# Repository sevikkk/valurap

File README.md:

Next iteration of 3d printer
============================

Hardware
--------

* 20x20 and 20x40 v-profile, linear rails based on PVC rollers
* E3D Titan Aero Extruder

Electronics
-----------

* Orange PI Zero as main brains and network
* Mojo v3 as FPGA
* TMC2130 Stepper drivers

Directories
-----------

* fpga/ - verilog sources for SLX9 on Mojo 
* mojo_soft/ - software for mega32u4 on Mojo
* host_soft/ - python sources running on Zero
* pcbs/ - KiCad files for PCBs

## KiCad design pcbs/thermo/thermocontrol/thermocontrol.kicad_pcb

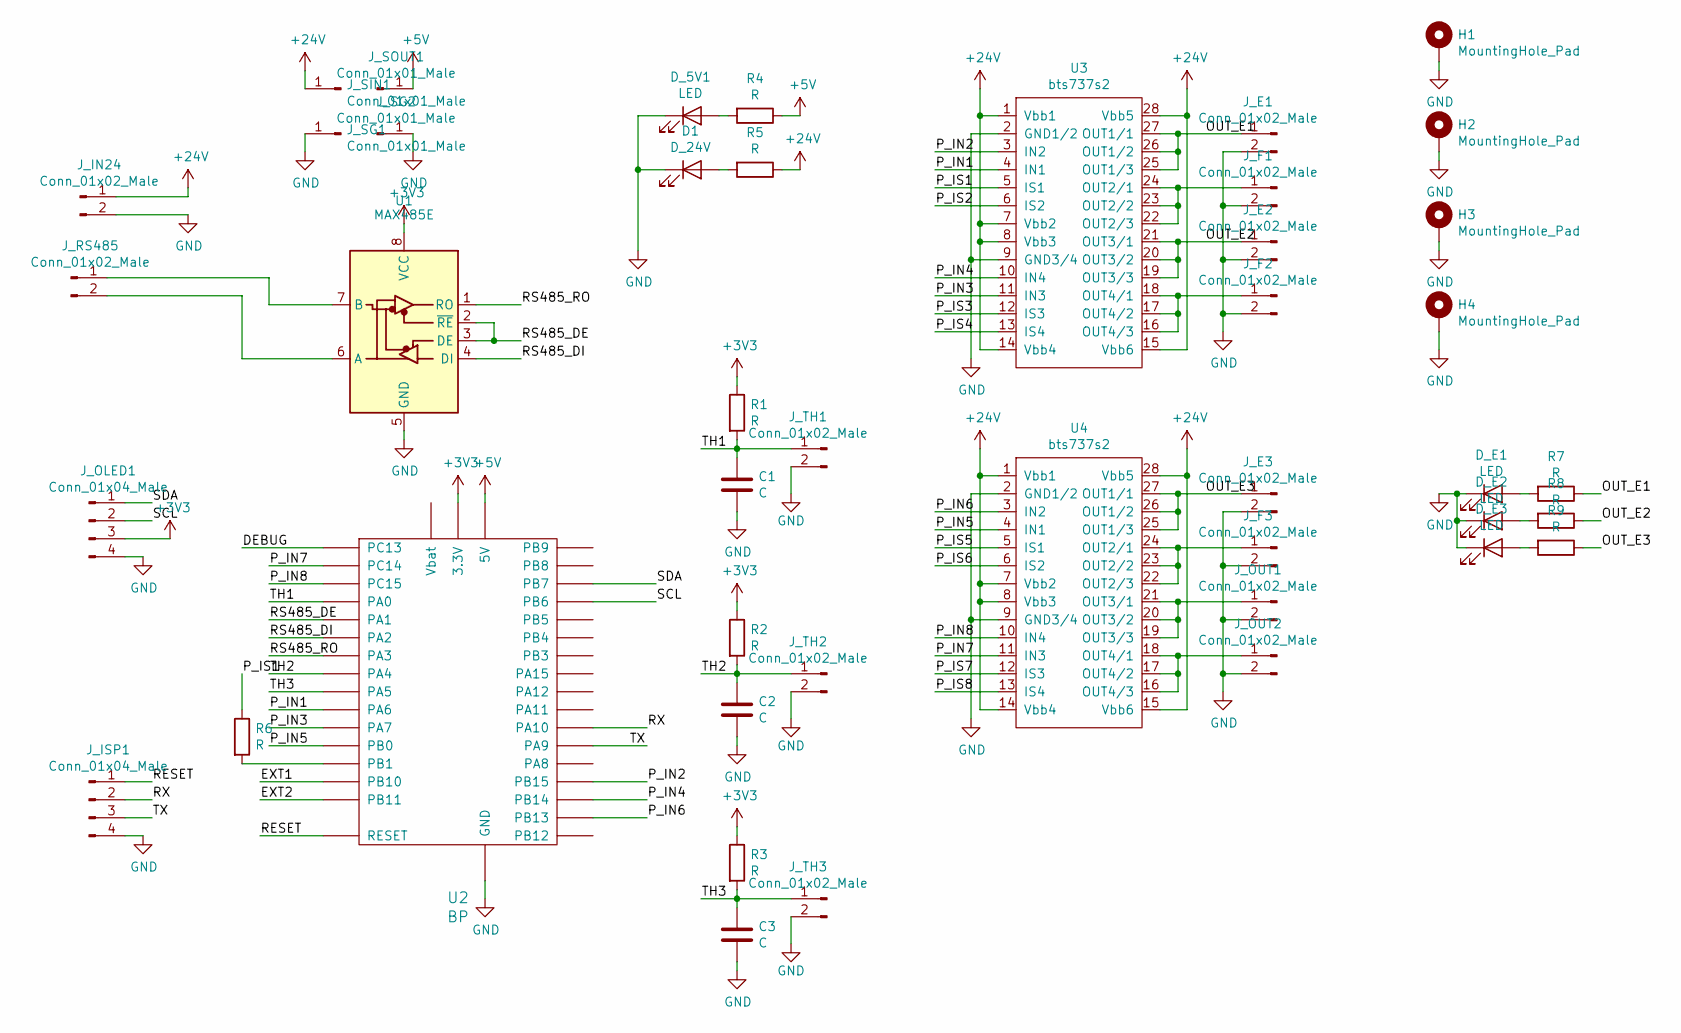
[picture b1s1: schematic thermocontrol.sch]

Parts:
C1, C2, C3: C; C_0805_2012Metric
D1: D_24V; LED_0805_2012Metric
D_5V1: LED; LED_0805_2012Metric
D_E1, D_E2, D_E3: LED; LED_0805_2012Metric
H1, H2, H3, H4: MountingHole_Pad; MountingHole_3.2mm_M3_DIN965_Pad
J_E1, J_E2, J_E3: Conn_01x02_Male; TerminalBlock_MetzConnect_Type011_RT05502HBWC_1x02_P5.00mm_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
J_F1, J_F2, J_F3: Conn_01x02_Male; PinHeader_1x02_P2.54mm_Vertical
J_IN24: Conn_01x02_Male; TerminalBlock_MetzConnect_Type011_RT05502HBWC_1x02_P5.00mm_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
J_ISP1: Conn_01x04_Male; PinHeader_2x02_P2.54mm_Vertical
J_OLED1: Conn_01x04_Male; PinHeader_2x02_P2.54mm_Vertical
J_OUT1, J_OUT2: Conn_01x02_Male; PinHeader_1x02_P2.54mm_Vertical
J_RS485: Conn_01x02_Male; PinHeader_1x02_P2.54mm_Vertical
J_SG1, J_SG2: Conn_01x01_Male; PinHeader_1x01_P2.54mm_Vertical
J_SIN1: Conn_01x01_Male; PinHeader_1x01_P2.54mm_Vertical
J_SOUT1: Conn_01x01_Male; PinHeader_1x01_P2.54mm_Vertical
J_TH1, J_TH2, J_TH3: Conn_01x02_Male; PinHeader_1x02_P2.54mm_Vertical
R1, R2, R3, R4, R5, R6, R7, R8, R9: R; R_0805_2012Metric
U1: MAX485E; SOIC-8_3.9x4.9mm_P1.27mm
U2: BP; BLUEPILL1
U3, U4: bts737s2; SOIC-28W_7.5x18.7mm_P1.27mm

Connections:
+3V3: J_OLED1.3, R1.1, R2.1, R3.1, U1.8 (VCC), U2.3V3 (3.3V)
+5V: J_SOUT1.1, R4.1, U2.5V
+24V: J_IN24.1, J_SIN1.1, R5.1, U3.1 (Vbb1), U3.7 (Vbb2), U3.8 (Vbb3), U3.14 (Vbb4), U3.15 (Vbb6), U3.28 (Vbb5), U4.1 (Vbb1), U4.7 (Vbb2), U4.8 (Vbb3), U4.14 (Vbb4), U4.15 (Vbb6), U4.28 (Vbb5)
/DEBUG: U2.PC13
/EXT1: U2.PB10
/EXT2: U2.PB11
/OUT_E1: J_E1.1, R7.1, U3.25 (OUT1/3), U3.26 (OUT1/2), U3.27 (OUT1/1)
/OUT_E2: J_E2.1, R8.1, U3.19 (OUT3/3), U3.20 (OUT3/2), U3.21 (OUT3/1)
/OUT_E3: J_E3.1, R9.1, U4.25 (OUT1/3), U4.26 (OUT1/2), U4.27 (OUT1/1)
/P_IN1: U2.PA6, U3.4 (IN1)
/P_IN2: U2.PB15, U3.3 (IN2)
/P_IN3: U2.PA7, U3.11 (IN3)
/P_IN4: U2.PB14, U3.10 (IN4)
/P_IN5: U2.PB0, U4.4 (IN1)
/P_IN6: U2.PB13, U4.3 (IN2)
/P_IN7: U2.PC14, U4.11 (IN3)
/P_IN8: U2.PC15, U4.10 (IN4)
/P_IS1: R6.1, U3.5 (IS1)
/P_IS2: U3.6 (IS2)
/P_IS3: U3.12 (IS3)
/P_IS4: U3.13 (IS4)
/P_IS5: U4.5 (IS1)
/P_IS6: U4.6 (IS2)
/P_IS7: U4.12 (IS3)
/P_IS8: U4.13 (IS4)
/RESET: J_ISP1.1, U2.NRST (RESET)
/RS485_DE: U1.2 (~RE), U1.3 (DE), U2.PA1
/RS485_DI: U1.4 (DI), U2.PA2
/RS485_RO: U1.1 (RO), U2.PA3
/RX: J_ISP1.2, U2.PA10
/SCL: J_OLED1.2, U2.PB6
/SDA: J_OLED1.1, U2.PB7
/TH1: C1.1, J_TH1.1, R1.2, U2.PA0
/TH2: C2.1, J_TH2.1, R2.2, U2.PA4
/TH3: C3.1, J_TH3.1, R3.2, U2.PA5
/TX: J_ISP1.3, U2.PA9
GND: C1.2, C2.2, C3.2, D1.1 (K), D_5V1.1 (K), D_E1.1 (K), D_E2.1 (K), D_E3.1 (K), H1.1, H2.1, H3.1, H4.1, J_E1.2, J_E2.2, J_E3.2, J_F1.2, J_F2.2, J_F3.2, J_IN24.2, J_ISP1.4, J_OLED1.4, J_OUT1.2, J_OUT2.2, J_SG1.1, J_SG2.1, J_TH1.2, J_TH2.2, J_TH3.2, U1.5 (GND), U2.G (GND), U3.2 (GND1/2), U3.9 (GND3/4), U4.2 (GND1/2), U4.9 (GND3/4)
unnamed: D1.2 (A), R5.2
unnamed: D_5V1.2 (A), R4.2
unnamed: D_E1.2 (A), R7.2
unnamed: D_E2.2 (A), R8.2
unnamed: D_E3.2 (A), R9.2
unnamed: J_F1.1, U3.22 (OUT2/3), U3.23 (OUT2/2), U3.24 (OUT2/1)
unnamed: J_F2.1, U3.16 (OUT4/3), U3.17 (OUT4/2), U3.18 (OUT4/1)
unnamed: J_F3.1, U4.22 (OUT2/3), U4.23 (OUT2/2), U4.24 (OUT2/1)
unnamed: J_OUT1.1, U4.19 (OUT3/3), U4.20 (OUT3/2), U4.21 (OUT3/1)
unnamed: J_OUT2.1, U4.16 (OUT4/3), U4.17 (OUT4/2), U4.18 (OUT4/1)
unnamed: J_RS485.1, U1.7 (B)
unnamed: J_RS485.2, U1.6 (A)
unnamed: R6.2, U2.PB1

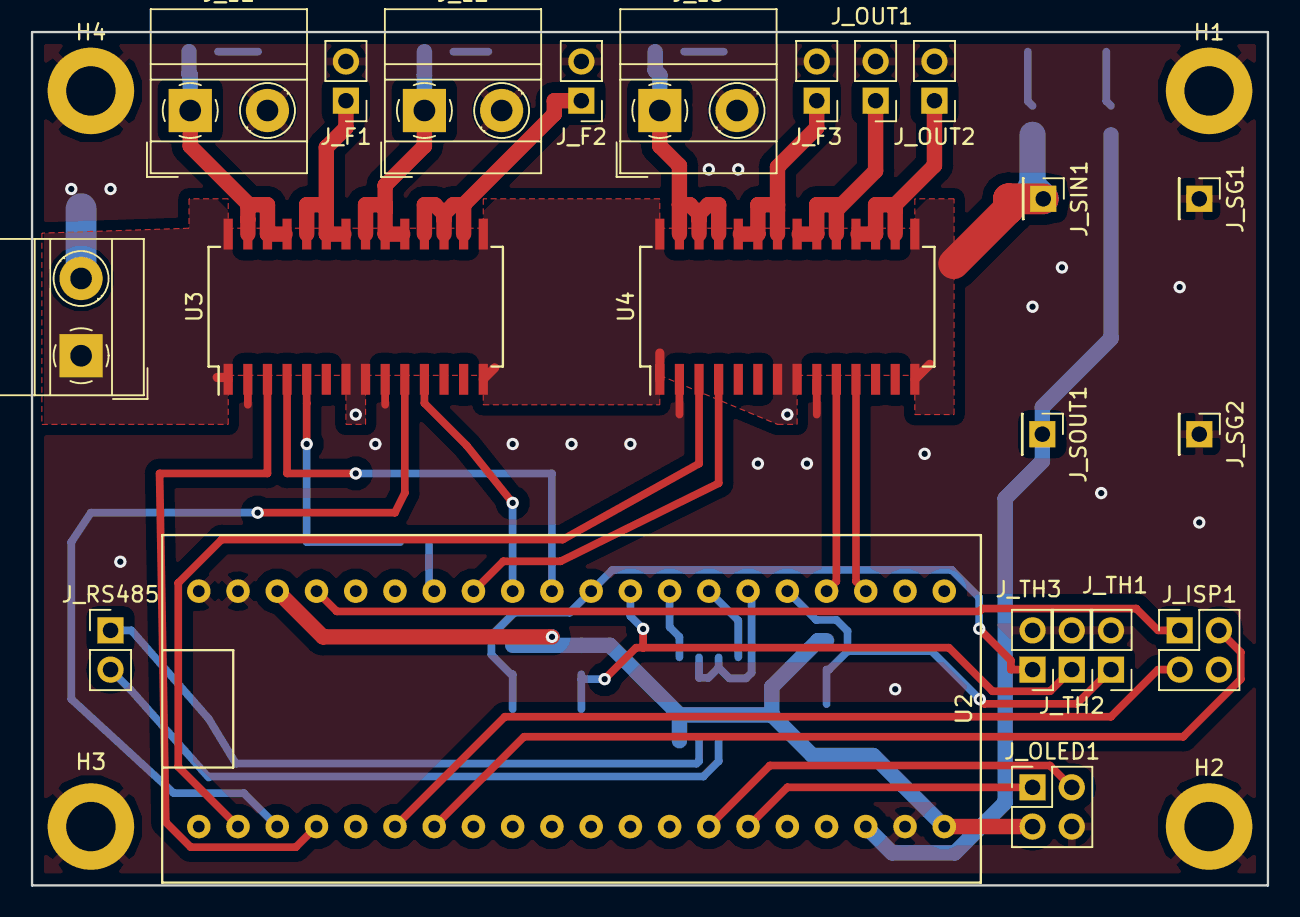
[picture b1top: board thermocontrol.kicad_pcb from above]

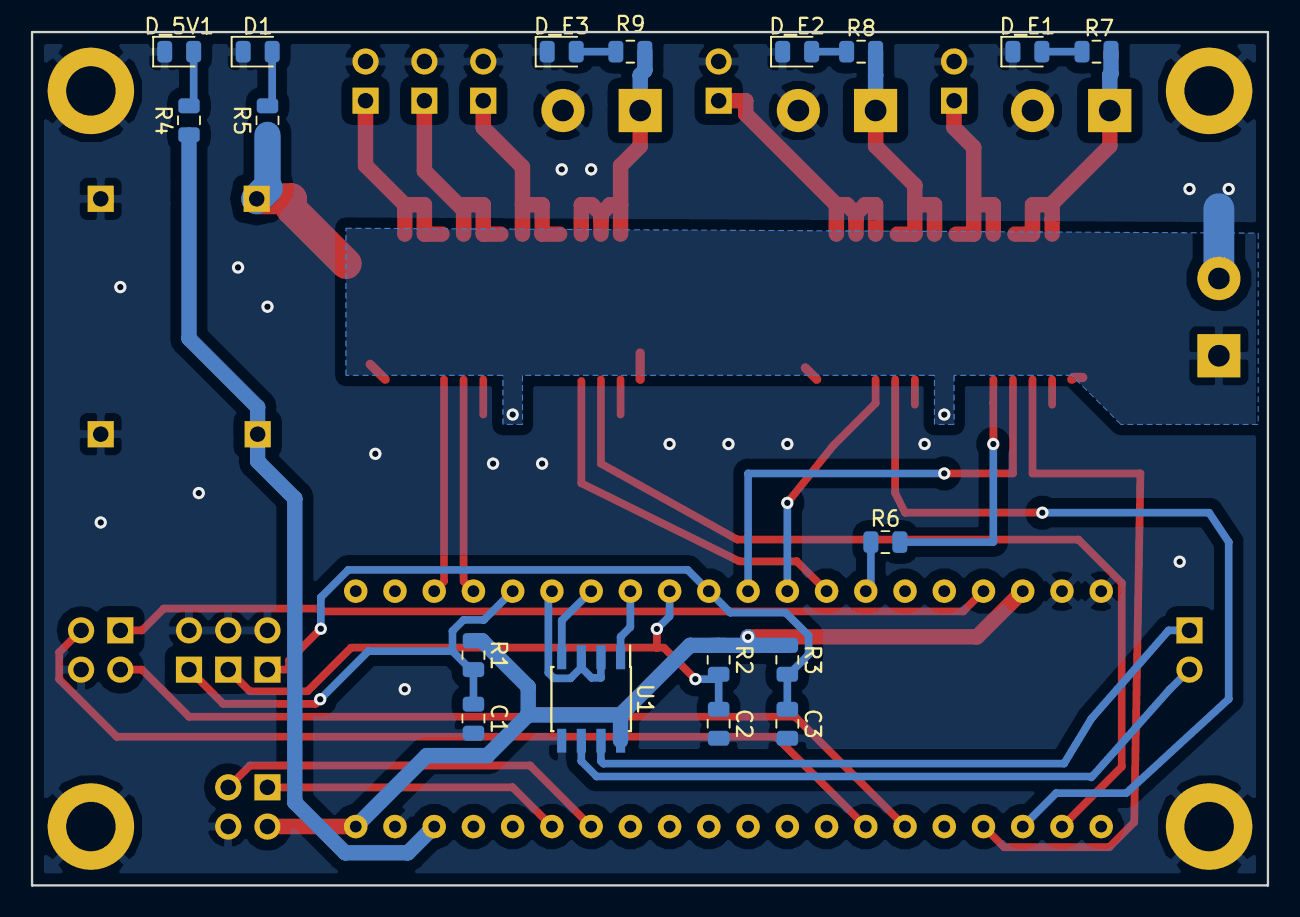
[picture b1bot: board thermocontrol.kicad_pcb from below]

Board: 2 copper layers, 80.0 x 55.2 mm, 44 parts (18 on the bottom side), 40 nets.

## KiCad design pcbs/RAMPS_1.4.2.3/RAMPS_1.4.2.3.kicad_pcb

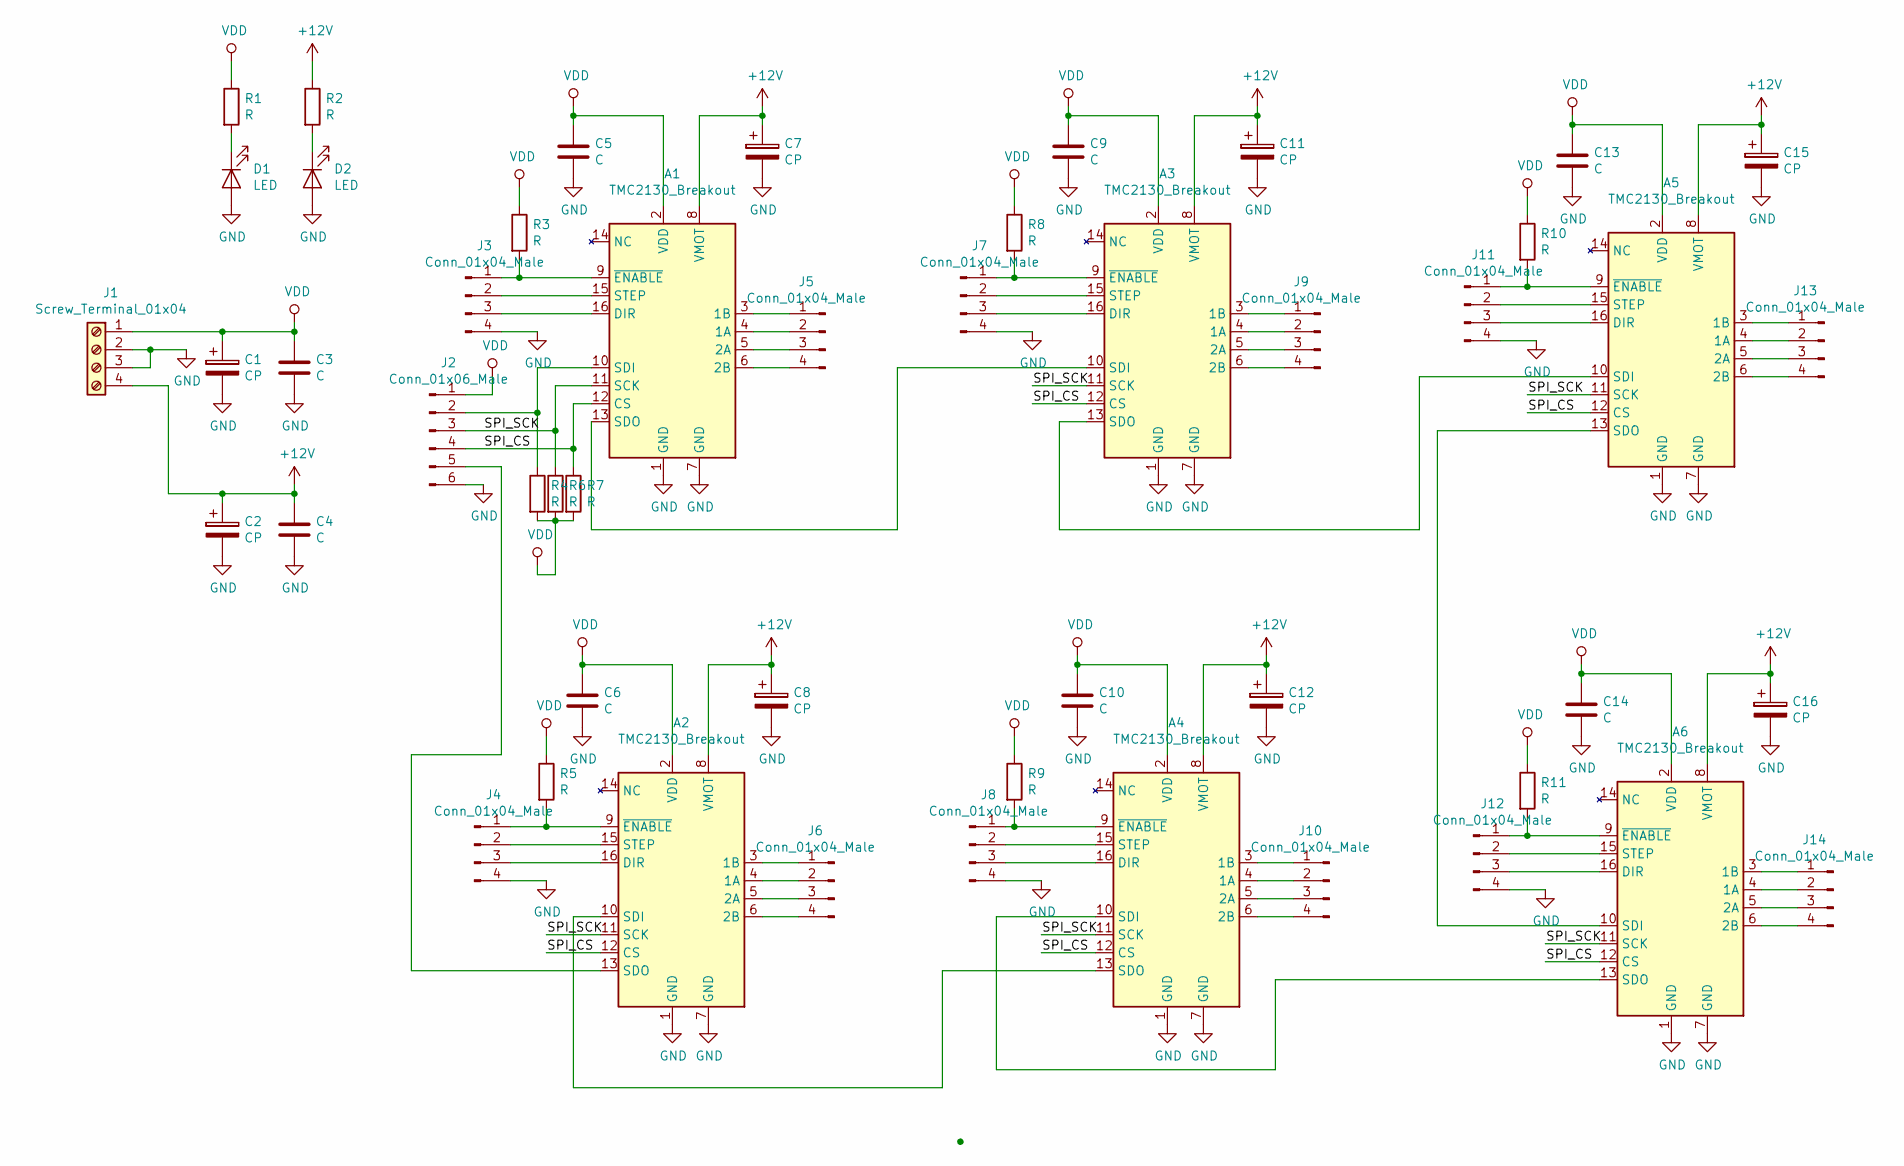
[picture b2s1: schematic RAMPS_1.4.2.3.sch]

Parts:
A1, A2, A3, A4, A5, A6: TMC2130_Breakout; Pololu_Breakout-16_15.2x20.3mm
C1, C2, C7, C8, C11, C12, C15, C16: CP; CP_Radial_D10.0mm_P5.00mm
C3, C4, C5, C6, C9, C10, C13, C14: C; C_0805_2012Metric
D1, D2: LED; LED_D1.8mm_W3.3mm_H2.4mm
J1: Screw_Terminal_01x04; TerminalBlock_4Ucon_1x04_P3.50mm_Horizontal
J2: Conn_01x06_Male; PinHeader_1x06_P2.54mm_Vertical
J3, J4, J5, J6, J7, J8, J9, J10, J11, J12, J13, J14: Conn_01x04_Male; PinHeader_1x04_P2.54mm_Vertical
R1, R2, R3, R4, R5, R6, R7, R8, R9, R10, R11: R; R_0805_2012Metric

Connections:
+12V: A1.8 (VMOT), A2.8 (VMOT), A3.8 (VMOT), A4.8 (VMOT), A5.8 (VMOT), A6.8 (VMOT), C2.1, C4.1, C7.1, C8.1, C11.1, C12.1, C15.1, C16.1, J1.4, R2.1
/SPI_CS: A1.12 (CS), A2.12 (CS), A3.12 (CS), A4.12 (CS), A5.12 (CS), A6.12 (CS), J2.4, R7.1
/SPI_SCK: A1.11 (SCK), A2.11 (SCK), A3.11 (SCK), A4.11 (SCK), A5.11 (SCK), A6.11 (SCK), J2.3, R6.1
GND: A1.1 (GND), A1.7 (GND), A2.1 (GND), A2.7 (GND), A3.1 (GND), A3.7 (GND), A4.1 (GND), A4.7 (GND), A5.1 (GND), A5.7 (GND), A6.1 (GND), A6.7 (GND), C1.2, C2.2, C3.2, C4.2, C5.2, C6.2, C7.2, C8.2, C9.2, C10.2, C11.2, C12.2, C13.2, C14.2, C15.2, C16.2, D1.2 (A), D2.2 (A), J1.2, J1.3, J2.6, J3.4, J4.4, J7.4, J8.4, J11.4, J12.4
unnamed: A1.3 (1B), J5.1
unnamed: A1.4 (1A), J5.2
unnamed: A1.5 (2A), J5.3
unnamed: A1.6 (2B), J5.4
unnamed: A1.9 (~ENABLE), J3.1, R3.2
unnamed: A1.10 (SDI), J2.2, R4.1
unnamed: A1.13 (SDO), A3.10 (SDI)
unnamed: A1.15 (STEP), J3.2
unnamed: A1.16 (DIR), J3.3
unnamed: A2.3 (1B), J6.1
unnamed: A2.4 (1A), J6.2
unnamed: A2.5 (2A), J6.3
unnamed: A2.6 (2B), J6.4
unnamed: A2.9 (~ENABLE), J4.1, R5.2
unnamed: A2.10 (SDI), A4.13 (SDO)
unnamed: A2.13 (SDO), J2.5
unnamed: A2.15 (STEP), J4.2
unnamed: A2.16 (DIR), J4.3
unnamed: A3.3 (1B), J9.1
unnamed: A3.4 (1A), J9.2
unnamed: A3.5 (2A), J9.3
unnamed: A3.6 (2B), J9.4
unnamed: A3.9 (~ENABLE), J7.1, R8.2
unnamed: A3.13 (SDO), A5.10 (SDI)
unnamed: A3.15 (STEP), J7.2
unnamed: A3.16 (DIR), J7.3
unnamed: A4.3 (1B), J10.1
unnamed: A4.4 (1A), J10.2
unnamed: A4.5 (2A), J10.3
unnamed: A4.6 (2B), J10.4
unnamed: A4.9 (~ENABLE), J8.1, R9.2
unnamed: A4.10 (SDI), A6.13 (SDO)
unnamed: A4.15 (STEP), J8.2
unnamed: A4.16 (DIR), J8.3
unnamed: A5.3 (1B), J13.1
unnamed: A5.4 (1A), J13.2
unnamed: A5.5 (2A), J13.3
unnamed: A5.6 (2B), J13.4
unnamed: A5.9 (~ENABLE), J11.1, R10.2
unnamed: A5.13 (SDO), A6.10 (SDI)
unnamed: A5.15 (STEP), J11.2
unnamed: A5.16 (DIR), J11.3
unnamed: A6.3 (1B), J14.1
unnamed: A6.4 (1A), J14.2
unnamed: A6.5 (2A), J14.3
unnamed: A6.6 (2B), J14.4
unnamed: A6.9 (~ENABLE), J12.1, R11.2
unnamed: A6.15 (STEP), J12.2
unnamed: A6.16 (DIR), J12.3
unnamed: D1.1 (K), R1.2
unnamed: D2.1 (K), R2.2
VDD: A1.2 (VDD), A2.2 (VDD), A3.2 (VDD), A4.2 (VDD), A5.2 (VDD), A6.2 (VDD), C1.1, C3.1, C5.1, C6.1, C9.1, C10.1, C13.1, C14.1, J1.1, J2.1, R1.1, R3.1, R4.2, R5.1, R6.2, R7.2, R8.1, R9.1, R10.1, R11.1

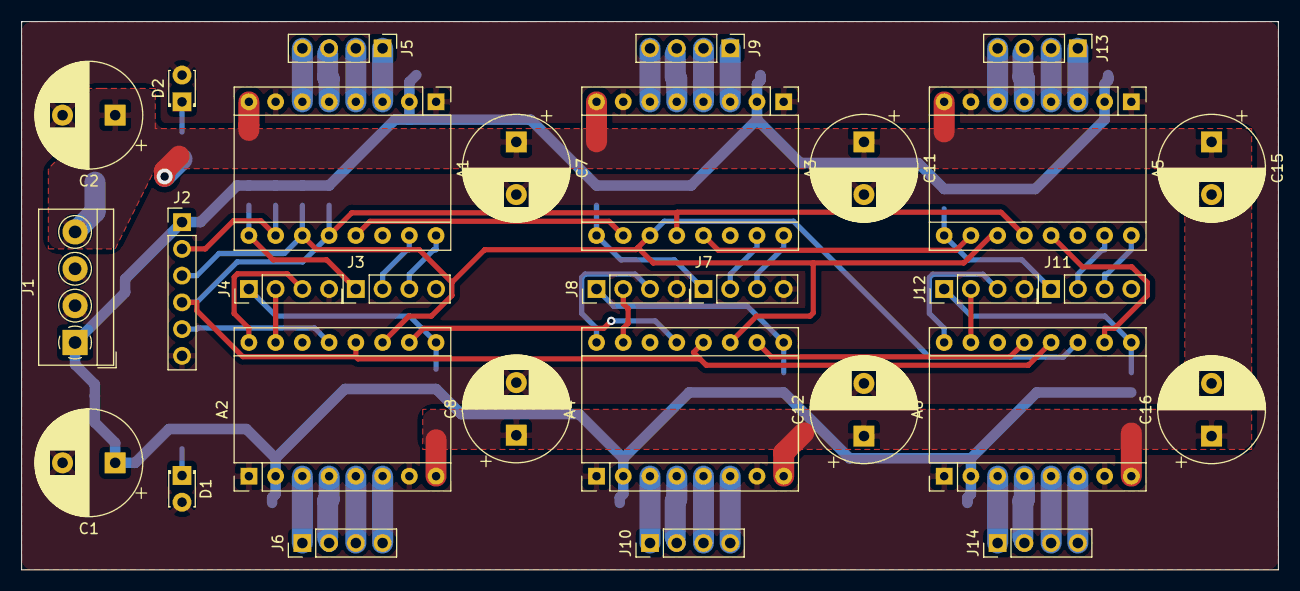
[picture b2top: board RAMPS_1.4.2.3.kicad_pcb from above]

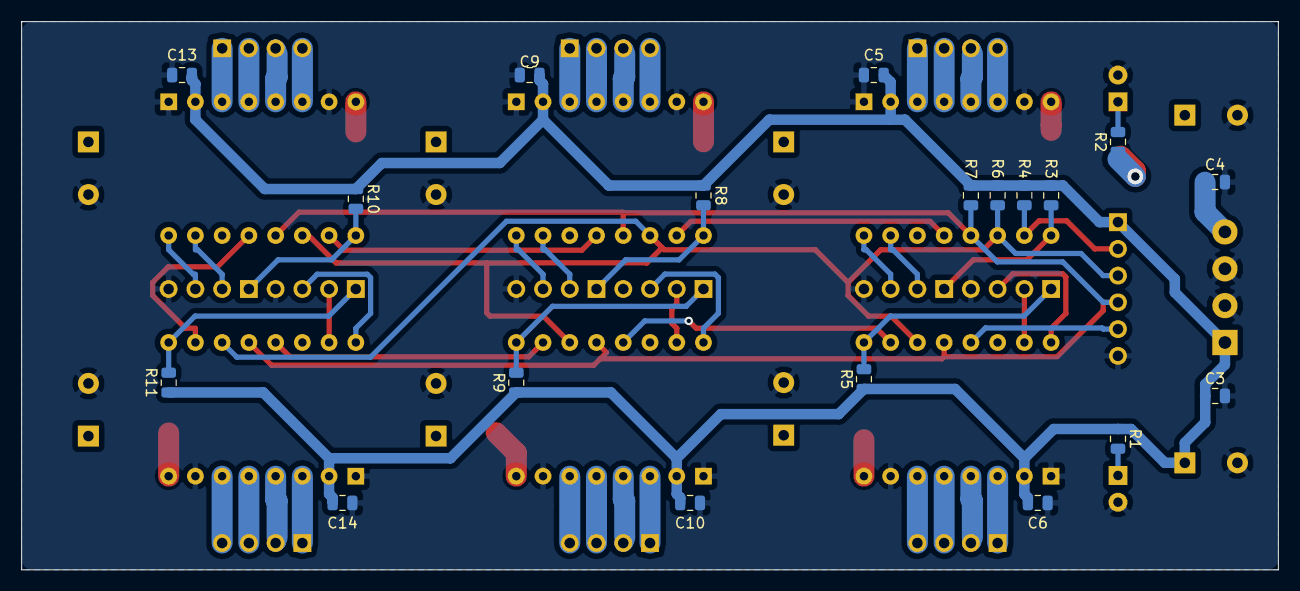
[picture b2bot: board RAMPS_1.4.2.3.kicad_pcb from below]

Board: 2 copper layers, 119.4 x 52.1 mm, 49 parts (19 on the bottom side), 56 nets.

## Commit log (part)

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2019-11-06 Hacky, but fast and working way to install opencv-python
2019-11-06 PID calibration notebook
2019-11-06 do not reset pid on small target changes
2019-11-09 HeatBed on PID channel 3
2019-11-09 adjust integrals on big steps
2019-11-09 automagic switch of APGs
2019-11-10 negative safe
2019-11-10 More useful debug, better homing
2019-11-17 optimized solve_model_simple
2019-11-17 report violations
2019-11-17 last segment works
2019-11-18 fast to slow approach for path planning, does not work
2019-11-30 pathplanning with speedups
2019-12-01 slightly better on stop
2019-12-01 format plan for APGs
2019-12-09 more real test
2019-12-15 less magic numbers
2019-12-15 extras in plan_to_int
2019-12-21 simple segment test case
2019-12-21 make pandas optional, remove unneeded assertion
2019-12-22 trying of real cura-generated toolpaths
    add constant accell mode for short speedups
    do not speed up segments if no slowdown
    smaller EPS
2019-12-27 Autogenerated app
2019-12-28 add backend container
2019-12-28 socket.io send
2019-12-29 Button as component
2019-12-29 cosmetics
2019-12-29 visual feedback
2019-12-29 bug fix
2019-12-30 remove template
2019-12-30 configurable default button class
2019-12-30 Allow aborting of execution
2019-12-30 better abort handling
2020-02-02 Working Abort button
2020-02-15 Do simple accel profile always
2020-02-15 parametrize splitting
2020-03-08 Build segments using pandas
2020-03-08 calculate max accel for segment
2020-03-09 segments to profile formatter
2020-03-09 more correct hardware emulation, limit corrections by max_axxel
2020-03-15 to/from tuple conversion so it can be safely pickled
2020-03-15 fix emulator for untouched segments, formatting speedup, add extruder handling
2020-03-17 gcode to layers full pipeline
2020-03-17 ignore generated layers
2020-04-05 ignore explicit X in layer files, gen asg mapping code
2020-04-05 save axis map data in layers, add mapping code to compiled code
2020-04-05 cythonization doc
2020-04-20 dump details on assert
2020-05-03 systemd unit file
2020-05-23 pass original line number down the path
2020-05-23 allow speed scaling and do corner slowdown based on accel/decel space
2020-06-07 second approach, not quite works yet
2020-07-04 fix tests
2020-07-04 more test cases
2020-07-05 reverse pass seems to work
2020-07-05 forward pass seems to work
2020-07-12 emu_in_loop works
2020-07-18 everything works
    for some limited definition of everything
    path_planning with emulator in loop works for single
    segment for X and Y
2020-07-19 Bump lodash in /host_soft/valurap/valurap/web/valurap-ui
    Bumps [lodash](https://github.com/lodash/lodash) from 4.17.15 to 4.17.19.
    - [Release notes](https://github.com/lodash/lodash/releases)
    - [Commits](https://github.com/lodash/lodash/compare/4.17.15...4.17.19)
2020-07-20 allow de adjustments
2020-07-20 restart from apgs support
2020-07-25 adjust min segment
2020-07-25 reuse old layers on restart
2020-07-25 better error report
2020-07-26 switch linux to fpga baudrate to 500kbps, speed up other things
2020-07-26 real life tweaks
2020-07-26 upgrade deps
2020-08-02 easy introspection from outside, appendable code buffer
2020-08-02 use path_planner2, less magic values
2020-08-02 typo
2020-08-02 current cura settings
2020-08-09 systemd service files
2020-08-09 reallife max speeds for 1.75 and 3mm extruders
2020-08-09 simple homing script
2020-08-09 code execution
2020-08-15 get current status
2020-09-12 Bump node-fetch in /host_soft/valurap/valurap/web/valurap-ui
    Bumps [node-fetch](https://github.com/bitinn/node-fetch) from 2.6.0 to 2.6.1.
    - [Release notes](https://github.com/bitinn/node-fetch/releases)
    - [Changelog](https://github.com/node-fetch/node-fetch/blob/master/docs/CHANGELOG.md)
    - [Commits](https://github.com/bitinn/node-fetch/compare/v2.6.0...v2.6.1)
2020-09-12 second extruder works, no in-progerss switch yet
2020-09-12 dual extrusion works
2020-09-20 TFT test
2020-09-20 clock speed
2020-09-27 debug messages adjustments
2020-09-27 adjust parameters
2020-10-10 helper scripts for remote print from cli
2020-10-10 explicit port
2020-10-10 update for real hw configuration
2020-10-10 new empty top level
2020-10-11 multi channel APG prototype
2020-10-11 target_v support
2020-10-11 aborts
2020-10-18 Buf_exec NG
2020-10-18 buf_exec + profile gen testbench
2020-10-19 some wip modules
2020-10-24 remove warning
2020-10-24 set delay as before
2020-10-25 fifo driven from s3g_executor
2020-10-26 buf_exec test
2020-10-31 correct generation of abort_done
2020-10-31 step_gen, first approach, syntax is correct :)
2020-11-01 Skip unneeded calc, remove extra speed load
2020-11-01 ensure there is no errors
2020-11-01 final X value check
2020-11-01 e2e top test
2020-11-01 consistent direction handling, enables are active low
2020-11-08 submit fully compiled code to server
2020-11-14 clanup and simplify
2020-11-14 rearrange motor_cfg slightly more
2020-11-14 testcase with multiple channels in use
2020-11-15 endstops check
2020-11-15 aarch64 image for docker
2020-11-21 docs, and switch uart to 1.5mbit/s
2020-11-21 use arm64 docker
2020-11-22 remove debug
2020-11-22 wire in asg errors, kill one more SP, will optimize later (may be)
2020-11-22 more regs
2020-11-28 emulator for new hardware version
2020-11-28 write_param with address tracking, debug dump
2020-11-29 hw reset code gen
2020-12-05 refactor and single runner function
2020-12-06 fixed step bit to 40, reduced speed accumulators to 40 bit, better feedback for fifo_write
2020-12-06 fifo write can block until space is available
2020-12-06 gitignore
2020-12-06 conversion helpers
2020-12-12 never ending send_fifo
2020-12-12 multiaxe ext_to_code
2020-12-13 axes setup
2020-12-13 sing extend for field extract, setting abort_a
2020-12-13 homing and moving
2020-12-19 more flexible ext_to_code
2020-12-19 asg_reset done right
2020-12-19 API support for move/moveto
2020-12-20 adjust Z end-stops positions, realtime display for OLED
2021-02-26 Bump aiohttp from 3.5.4 to 3.7.4 in /host_soft/valurap
    Bumps [aiohttp](https://github.com/aio-libs/aiohttp) from 3.5.4 to 3.7.4.
    - [Release notes](https://github.com/aio-libs/aiohttp/releases)
    - [Changelog](https://github.com/aio-libs/aiohttp/blob/master/CHANGES.rst)
    - [Commits](https://github.com/aio-libs/aiohttp/compare/v3.5.4...v3.7.4)
2021-02-27 gen_layers adjustments
2021-03-10 Bump elliptic in /host_soft/valurap/valurap/web/valurap-ui
    Bumps [elliptic](https://github.com/indutny/elliptic) from 6.5.3 to 6.5.4.
    - [Release notes](https://github.com/indutny/elliptic/releases)
    - [Commits](https://github.com/indutny/elliptic/compare/v6.5.3...v6.5.4)
2021-03-16 systemd service switch
2021-03-16 calibration
2021-03-16 gen_layers and printing works for new electronics
2021-03-16 fix emu mode
2021-03-20 more status bits
2021-03-20 raise for status in exec_binary
2021-03-20 slower Z at print-time
2021-03-31 Bump y18n in /host_soft/valurap/valurap/web/valurap-ui
    Bumps [y18n](https://github.com/yargs/y18n) from 4.0.0 to 4.0.1.
    - [Release notes](https://github.com/yargs/y18n/releases)
    - [Changelog](https://github.com/yargs/y18n/blob/master/CHANGELOG.md)
    - [Commits](https://github.com/yargs/y18n/commits)
2021-05-09 Bump url-parse in /host_soft/valurap/valurap/web/valurap-ui
    Bumps [url-parse](https://github.com/unshiftio/url-parse) from 1.4.7 to 1.5.1.
    - [Release notes](https://github.com/unshiftio/url-parse/releases)
    - [Commits](https://github.com/unshiftio/url-parse/compare/1.4.7...1.5.1)
2021-05-11 Bump hosted-git-info in /host_soft/valurap/valurap/web/valurap-ui
    Bumps [hosted-git-info](https://github.com/npm/hosted-git-info) from 2.8.8 to 2.8.9.
    - [Release notes](https://github.com/npm/hosted-git-info/releases)
    - [Changelog](https://github.com/npm/hosted-git-info/blob/v2.8.9/CHANGELOG.md)
    - [Commits](https://github.com/npm/hosted-git-info/compare/v2.8.8...v2.8.9)
2021-05-28 Bump dns-packet in /host_soft/valurap/valurap/web/valurap-ui
    Bumps [dns-packet](https://github.com/mafintosh/dns-packet) from 1.3.1 to 1.3.4.
    - [Release notes](https://github.com/mafintosh/dns-packet/releases)
    - [Changelog](https://github.com/mafintosh/dns-packet/blob/master/CHANGELOG.md)
    - [Commits](https://github.com/mafintosh/dns-packet/compare/v1.3.1...v1.3.4)
2021-06-12 fix WRITE_HI
2021-06-12 add help on ?
2021-06-12 abort helper
2021-06-21 switch to step_bit=48
2021-06-22 current state, oversample on start/stop
2021-06-27 resample based path planning
2021-06-27 turbo profile
2021-07-01 Bump socket.io-parser in /host_soft/valurap/valurap/web/valurap-ui
    Bumps [socket.io-parser](https://github.com/socketio/socket.io-parser) from 3.3.0 to 3.3.2.
    - [Release notes](https://github.com/socketio/socket.io-parser/releases)
    - [Changelog](https://github.com/socketio/socket.io-parser/blob/3.3.2/CHANGELOG.md)
    - [Commits](https://github.com/socketio/socket.io-parser/compare/3.3.0...3.3.2)
    ---
    updated-dependencies:
2021-08-14 filter knots
2021-08-14 show bed temp
2021-08-14 lin_k adjustments
2021-08-14 remove X overflow workarounds
2021-08-14 report details before erroring out
2022-01-14 Bump follow-redirects in /host_soft/valurap/valurap/web/valurap-ui
    Bumps [follow-redirects](https://github.com/follow-redirects/follow-redirects) from 1.12.1 to 1.14.7.
    - [Release notes](https://github.com/follow-redirects/follow-redirects/releases)
    - [Commits](https://github.com/follow-redirects/follow-redirects/compare/v1.12.1...v1.14.7)
    ---
    updated-dependencies:
    - dependency-name: follow-redirects
2022-02-05 random additional files
2022-02-05 Saved in new version of FreeCAD
2022-02-06 Rebuilt left_y_carriage_plate
2022-02-06 autogenerate breps for printed parts
2022-02-06 opto endstop
2022-02-13 Bump follow-redirects in /host_soft/valurap/valurap/web/valurap-ui
    Bumps [follow-redirects](https://github.com/follow-redirects/follow-redirects) from 1.12.1 to 1.14.8.
    - [Release notes](https://github.com/follow-redirects/follow-redirects/releases)
    - [Commits](https://github.com/follow-redirects/follow-redirects/compare/v1.12.1...v1.14.8)
    ---
    updated-dependencies:
    - dependency-name: follow-redirects
2022-02-26 Bump url-parse in /host_soft/valurap/valurap/web/valurap-ui
    Bumps [url-parse](https://github.com/unshiftio/url-parse) from 1.4.7 to 1.5.10.
    - [Release notes](https://github.com/unshiftio/url-parse/releases)
    - [Commits](https://github.com/unshiftio/url-parse/compare/1.4.7...1.5.10)
    ---
    updated-dependencies:
    - dependency-name: url-parse
2022-04-29 Bump async in /host_soft/valurap/valurap/web/valurap-ui
    Bumps [async](https://github.com/caolan/async) from 2.6.3 to 2.6.4.
    - [Release notes](https://github.com/caolan/async/releases)
    - [Changelog](https://github.com/caolan/async/blob/v2.6.4/CHANGELOG.md)
    - [Commits](https://github.com/caolan/async/compare/v2.6.3...v2.6.4)
    ---
    updated-dependencies:
2022-06-22 Bump shell-quote in /host_soft/valurap/valurap/web/valurap-ui
    Bumps [shell-quote](https://github.com/substack/node-shell-quote) from 1.7.2 to 1.7.3.
    - [Release notes](https://github.com/substack/node-shell-quote/releases)
    - [Changelog](https://github.com/substack/node-shell-quote/blob/master/CHANGELOG.md)
    - [Commits](https://github.com/substack/node-shell-quote/compare/v1.7.2...1.7.3)
    ---
    updated-dependencies:
2022-12-05 Bump decode-uri-component in /host_soft/valurap/valurap/web/valurap-ui
    Bumps [decode-uri-component](https://github.com/SamVerschueren/decode-uri-component) from 0.2.0 to 0.2.2.
    - [Release notes](https://github.com/SamVerschueren/decode-uri-component/releases)
    - [Commits](https://github.com/SamVerschueren/decode-uri-component/compare/v0.2.0...v0.2.2)
    ---
    updated-dependencies:
    - dependency-name: decode-uri-component
